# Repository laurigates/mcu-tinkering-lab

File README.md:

# MCU Tinkering Lab

A monorepo of microcontroller projects, mostly ESP32. The largest is a robot car
that drives on camera input and an LLM's plan. Others cover audio toys, game
controller bridges, an ESP-NOW mesh of companion boxes, and a self-balancing
robot on the RP2350.

## Flash from the browser

Released firmware can be flashed with the
[web flasher](https://laurigates.github.io/mcu-tinkering-lab/) in Chrome or
Edge, with no toolchain installed. Board-specific boot-mode notes are on the
page itself ([source](docs/flasher/index.html)).

The [robocar board story](https://laurigates.github.io/mcu-tinkering-lab/robocar/)
follows the robot car from a 2018 kit to a generated, factory-made carrier
board ([source](docs/site/robocar/index.html)). The
[balancebot story](https://laurigates.github.io/mcu-tinkering-lab/balancebot/)
follows the self-balancing robot from its first firmware to standing in place
([source](docs/site/balancebot/index.html)).

## Build from source

ESP-IDF builds run in a container, so Docker and
[just](https://github.com/casey/just) are the only requirements.

```bash
git clone https://github.com/laurigates/mcu-tinkering-lab.git
cd mcu-tinkering-lab
just setup-all                   # Docker images, dev tools, pre-commit hooks
just list-projects               # every project module
just robocar::build              # build one
```

Build, test and CI details are in [CONTRIBUTING.md](CONTRIBUTING.md).

## Projects

| Domain | Projects |
|---|---|
| `robotics/` | [AI robot car](packages/robotics/robocar/README.md): single-board firmware (XIAO ESP32-S3 Sense), its [integrated carrier](packages/robotics/robocar/integrated/README.md), [bring-up self-test](packages/robotics/robocar/bringup/README.md), a [Pymunk plant model](packages/robotics/robocar/simulation/README.md) and a [behaviour twin](packages/robotics/robocar/twin/README.md). [Self-balancing robot](packages/robotics/balancebot/README.md) (XIAO RP2350, Pico SDK) |
| `thinkpack/` | ESP-NOW mesh of companion boxes: brainbox (LLM coordinator), boombox, chatterbox, finderbox, glowbug, mesh-demo |
| `camera-vision/` | MJPEG webserver, camera + I2S audio, LLM Telegram bot, Gemini object detection |
| `audio/` | BLE gamepad synth, kids' audio toy, melody detector, RFID audiobook player (ESPHome) |
| `input-gaming/` | Xbox → Switch bridge, Switch USB proxy, LEGO Boost with an Xbox controller |
| `networking/` | IT troubleshooter, WiFi AP test, WireGuard + Home Assistant (ESPHome) |
| `sensors/` | 24 GHz mmWave presence sensor (ESPHome) |
| `usb-tools/` | ESP32-S3 raw USB relay for facedancer |
| `games/` | NFC scavenger hunt |
| `components/` | Shared ESP-IDF components: Improv WiFi provisioning, GitHub Releases OTA, ThinkPack libraries |

Most projects have a README in their directory.

## Documentation

- [docs/](docs/README.md): architecture decisions, requirements, board
  references, schematics
- [CONTRIBUTING.md](CONTRIBUTING.md): development setup, build commands,
  testing, CI, adding a project

## License

MIT ([LICENSE](LICENSE)), except the two vendored KiCad libraries under
`tools/kicad/lib/`, which keep their upstream licences:
[`kicad-stock/`](tools/kicad/lib/kicad-stock/) is a subset of the KiCad
libraries under CC-BY-SA 4.0 with KiCad's design exception
([LICENSE.md](tools/kicad/lib/kicad-stock/LICENSE.md)), and
[`seeed-xiao/`](tools/kicad/lib/seeed-xiao/) is Seeed Studio's, under their MIT
licence ([LICENSE](tools/kicad/lib/seeed-xiao/LICENSE)).

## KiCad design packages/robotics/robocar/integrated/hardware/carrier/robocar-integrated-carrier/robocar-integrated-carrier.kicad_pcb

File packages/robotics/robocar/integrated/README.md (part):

# Robocar: integrated carrier

The [robocar](../) carrier PCB with the chips on the board itself:
no breakout modules and no buck module. It exists to compare the two approaches.
The firmware, the pin header (`../main/pin_config.h`) and the three head
boards are robocar's, unchanged. There is no firmware here.

> **PROVISIONAL: do not order.** The board is placed by hand, routed by Freerouting
> and passes every carrier gate (ERC, DRC with schematic parity, netlist parity,
> the board check and its stamp). One adversarial layout review has been run and
> its findings fixed (see [Before ordering](#before-ordering)); the fixed board
> has not been reviewed again, and the bench items there stand.

## What changes

| Socketed carrier (`../hardware/carrier`) | Integrated carrier (here) |
|---|---|
| A3 Adafruit TCA9548A breakout | U5 TCA9548APWR (TSSOP-24), C5, upstream I2C pull-ups R14/R15, RESET pull-up R16 |
| A2 Adafruit PCA9685 breakout | U6 PCA9685PW (TSSOP-28), C4; series R17-R24 on the LED and servo channels (220 Ω, 47 Ω on green and blue) |
| A1 SparkFun TB6612FNG breakout | U7 TB6612FNG (SSOP-24), C15 (VCC), C16 (VM) |
| A4 Adafruit MAX98357A breakout | U8 MAX98357AETE+ (TQFN-16), C17, C18, ferrite bead FB1 on its supply |
| A5 CJMCU-2317 (MCP23017) module | U9 MCP23017-E/SS (SSOP-28), C6 |
| J4 lead to an LM2596 module | U10 TPS563208 (SOT-23-6, 3 A), L1 4.7 µH, C9-C14 and C20, feedback R12/R13, EN cutoff divider R25/R26, input bulk C19 |
| (no fuse) | Q1 reverse-polarity P-FET and F1 3 A PTC between the XT30 and VBAT, [below](#design-notes) |
| C1-C3 470 µF electrolytics (8 x 10.5 mm) | C1-C3 22 µF tantalums (3528), [below](#bulk-capacitors) |
| Servos and LEDs on the PCA9685 breakout's 3-pin columns | J20/J21 servo headers, J22/J23 RGB LED headers |
| Speaker on the MAX98357A breakout's screw terminal | J19 JST-XH 2 |

Everything else keeps its reference, value and role: the connectors, the test
headers, the LDO, the mux channel pull-ups, the buzzer, the mounting holes and
the three head boards (U1/J2, and the spares U3/J16 and U4/J17). Net names are the socketed carrier's, so the two netlists compare
by name.

## Footprint comparison

The laid-out boards, as cut apart (by hand saw, [below](#panel-hand-saw):
the line between the main board and the heads
takes about 1 mm from each, so the main board is 63.5 mm wide once separated):

| Main board | Socketed | Integrated |
|---|---|---|
| Size | about 70.5 x 100 mm | 64.5 x 76 mm |
| Area | about 7050 mm² | 4902 mm² (−30 %) |

| Whole PCB | Socketed | Integrated |
|---|---|---|
| Outline | 100 x 100 mm | 94 x 100 mm |

Both PCBs carry the same three head boards, the 29.5 mm square for the pan-tilt
cradle, in a column on the right: the integrated column is the socketed one moved
6 mm left. The integrated main board ends at y 76, so the strip below it
(64.5 x 24 mm) is waste; the outline stays 100 mm tall for the heads. J3's
courtyard ends 0.06 mm short of the y 76 line (`carrier-review`): saw that
line on the waste side. The integrated main board keeps
the socketed one's layout habits (connectors along the front and rear edges, M3
holes in the corners, 0.5 mm edge keepouts), so the difference is the chips, not a
tighter layout style. Its parts' courtyards fill half of it; the socketed board's
fill three quarters.

The parts alone:

```bash
just robocar-integrated::compare
```

prints each carrier's courtyard area, grouped into main board, head board and
mounting holes, then every main-board part only one carrier has
(`tools/kicad/area.py`). Each part counts its courtyard's bounding box: for a
breakout socket that is the module's outline, for a bare chip the package and its
pads. The sum is a lower bound on board area; it leaves out routing and the gaps a
placement leaves. As of this commit:

| Main board | Socketed | Integrated |
|---|---|---|
| Parts | 40 | 77 |
| Courtyard area | 5381 mm² | 2298 mm² (−57 %) |
| SMD / through-hole parts | 20 / 20 | 58 / 19 |
| Pads | 202 | 316 |

Where the area goes:

- The 31 parts the two main boards share take 1362 mm². Most of it is the
  connectors, the 2x10 GPIO mirror header and the M3 holes' surroundings, none of
  which shrink.
- The five breakout sockets and the buck lead take 3687 mm²; the PCA9685 breakout
  alone is 63 x 26 mm (1625 mm²). Their replacements, 46 parts, take 936 mm²:
  the six chips 356 mm², the buck's inductor 46 mm² and input bulk capacitor
  67 mm², 29 0805 passives and the ferrite bead 208 mm², the tantalums 52 mm²,
  D1 11 mm², and the new servo, LED and speaker connectors 197 mm².
- The three 470 µF electrolytics (332 mm²) became 22 µF tantalums (52 mm²).
- The socketed carrier's buck converter is off the board: the LM2596 module (about
  43 x 21 mm) sits on the chassis at the end of J4's lead. The integrated buck
  (U10, L1, eight capacitors, four resistors) adds about 220 mm² of courtyard
  to the board and removes the module.

Other differences the numbers do not show:

- **Assembly.** Every new part is SMD. TSSOP and SSOP at 0.65 mm pitch hand-solder
  with flux and care; the MAX98357A's TQFN with its exposed pad needs hot air or
  JLCPCB assembly. The socketed carrier needs no fine-pitch soldering.
- **Repair.** A dead breakout unplugs; a dead chip is a rework job.
- **Debug.** The breakouts' own pins are no longer there to probe. J11 and J12
  (supply and I2C test headers) are unchanged; there is no test point on the
  motor-driver inputs or the I2S lines.
- **Height.** The breakouts sat on sockets, about 10-15 mm above the board. The
  tallest integrated parts are the headers and the XT30; C19 is 7.7 mm.

## JLCPCB assembly

Every SMD part on the front carries an LCSC number (#808), so JLCPCB can
assemble the whole main board. `just robocar-integrated::carrier-fab`
writes `output/assembly/<name>-bom-jlc-<sha7>.csv` and
`<name>-cpl-jlc-<sha7>.csv`, named for the commit: 25 BOM lines, 60
placements, one per SMD part. The chips and the inductor take their number
from their registry entry (`docs/reference/parts/`), the passives from
`hardware.toml`.

| Ref | Part | LCSC | Library |
|---|---|---|---|
| U5 | TCA9548APWR | C130026 | Extended |
| U6 | PCA9685PW,118 | C2678753 | Extended |
| U7 | TB6612FNG (SSOP-24, 5.3 mm) | C88224 | Extended |
| U8 | MAX98357AETE+T | C910544 | Extended |
| U9 | MCP23017-E/SS | C506653 | Extended |
| U10 | TPS563208DDCR | C468250 | Extended |
| U2 | AMS1117-3.3 | C6186 | Basic |
| L1 | Bourns SRN6045TA-4R7M | C2044594 | Extended |
| F1 | BSMD1812-300-16V, 3 A hold, 16 V | C883162 | Extended |
| Q1 | DMP3013SFV-7 P-MOSFET, PowerDI3333-8 | C264098 | Extended |
| D1 | B5819W Schottky, SOD-123 | C8598 | Basic |
| FB1 | Murata BLM21PG221SN1D, 220 Ω, 2 A, 45 mΩ | C85840 | Extended |
| C19 | 100 µF 35 V electrolytic, 6.3 x 7.7 mm | C2836437 | Extended |
| C1-C3, C7, C8 | 22 µF 16 V tantalum, 3528 | C8020 | Extended |
| C13, C14, C20 | 22 µF 25 V X5R 0805 | C45783 | Basic |
| C9, C11, C16, C17, C21 | 10 µF 25 V X5R 0805 | C15850 | Basic |
| C4-C6, C10, C12, C15, C18 | 100 nF 50 V X7R 0805 | C49678 | Basic |
| R2-R11, R14, R15 | 2.2 kΩ 0805 | C17520 | Basic |
| R13, R16, R27 | 10 kΩ | C17414 | Basic |
| R12 | 56 kΩ | C17756 | Extended |
| R25 | 100 kΩ | C149504 | Basic |
| R26 | 36 kΩ | C4360 | Extended |
| R17, R20, R23, R24 | 220 Ω | C17557 | Basic |
| R18, R19, R21, R22 | 47 Ω | C17714 | Basic |
| R1 | 100 Ω | C17408 | Basic |

Stock and library type are JLCPCB's listing on 2026-10-19. The thinnest stock
is the inductor (179) and the MCP23017 (424); check both before ordering.
Q1 (C264098) is Extended, 3,409 in stock on 2026-10-22. 56 kΩ
(R12, see Buck converter) has no Basic part and costs one Extended fee, as TI's
54.9 kΩ did; so does 36 kΩ (R26, see Pack voltage), 93,700 in stock on
2026-10-21. JLCPCB lists no 56.2 kΩ.

### Placement rotation

JLCPCB places each part as LCSC's own footprint draws it, and LCSC draws most of
these chips with pin 1 bottom-left where KiCad has it top-left.
[`docs/reference/jlcpcb-rotations.toml`](../../../../docs/reference/jlcpcb-rotations.toml)
holds the offset per LCSC number, derived by `kicad.lcsc_rotation` from LCSC's
footprint pad by pad, and `kicad.jlc` adds it to KiCad's rotation in
`cpl-jlc.csv`: 270° for U5, U7, U8, U9, U10 and Q1, 180° for U2, 0° for U6
(the PCA9685PW's LCSC footprint has pin 1 top-left) and for every two-pad part.
Without it the CPL would have put five chips at 90° and the LDO at 180°.
`carrier-fab` fails on a placed LCSC number with no checked offset. JLCPCB's
preview is still the last check: compare each chip's pin-1 dot with the
silkscreen before paying.

### Fiducials

Three fiducials, FID1-FID3 (1 mm copper, 2 mm mask opening), sit on the main
board in an asymmetric triangle: top-left (3.5, 9.5), top-right (60.5, 10.0)
and bottom-left (3.5, 66.5), each 2 mm clear of every courtyard. JLCPCB does not
require them for a board this size; they let the machine correct for board
stretch, which the 0.5 mm-pitch TQFN is least tolerant of.

### What is still hand-soldered

The through-hole parts: the XT30 (J3), the motor, speaker, rangefinder and OLED
connectors (J5-J9, J19), the ribbon header (J1), the servo and LED headers
(J20-J23), the test and ground headers (J11-J15), the GPIO mirror header (J18),
the buzzer (BZ1), and on the heads the XIAO sockets (U1, U3, U4) and their
ribbon headers (J2, J16, J17). All are 2.5 mm pitch or wider.

After soldering the XT30 (J3), inspect it for solder bridges: the unfused
pack input (PACK_IN, the 1.2 mm track from J3's + pin to Q1) runs between
J3's GND pin and F1's pad 1 at close to the board's 0.2 mm minimum
clearance, and a bridge there shorts the pack ahead of F1. Moving Q1 and F1
to open the gap does not fit: F1 would land on the 5V trunk.

### Cost

The order is five PCBs, the minimum, of which 2 or 5 can be assembled. The
outline is 94 x 100 mm on two layers, but that does not settle the price:
JLCPCB counts the pieces of one file as separate designs "as long as it can be
separated, no matter by v-cut, millings, or drill holes", and says it will
"usually charge more for this"
([Different Design in Your PCB Files](https://jlcpcb.com/help/article/different-design-in-your-pcb-files)).
The same page treats designs inside one outline with no v-cut lines, tabs or
milling slots, separated by the customer, as one design: that is this board,
cut apart by hand ([below](#panel-hand-saw)). A mouse-bite panel of the same
four pieces would count as four. No price has been seen, and coupons and
other offers change it from order to order. The part prices are fixed:

- **Parts:** about $11.50 per board at JLCPCB's listed unit prices
  (2026-10-19), plus Q1 at $1.23 (2026-10-22). The chips are most of it: PCA9685 $3.33, MCP23017 $1.77,
  MAX98357A $1.32, TB6612FNG $1.15, TCA9548A $0.81. Attrition parts come on
  top.
- **Extended parts:** 14 BOM lines, each with a per-order loading fee unless an
  offer waives it: the six chips, Q1, L1, F1, FB1, C19, the tantalums (C8020),
  R12 and R26. The other 11 lines are Basic, D1 included (JLCPCB's parts
  search, 2026-10-22).

## Panel: hand-saw

The main board and the three heads share one 94 x 100 mm PCB with a single
outline, cut apart by hand after delivery: `board.toml [panel] mode = "saw"`.
JLCPCB counts one outline with no slots, tabs or v-cuts as one design
([Cost](#cost)). The six cut lines are silkscreen (`[silk] cut_lines`), each
inside a copper-free keepout band.

**Saw on the waste side of each line, then file to the line.** On the y 70.5
line (head 2 above, head 3 below) the nearest copper is HEAD3_I2C_SDA, 0.79 mm
from the line; on every other line it is 1.00 mm or more (`carrier-review`).
A saw kerf of about 1 mm centred on the y 70.5 line would leave about 0.3 mm of
board over that track. The y 76 line under the main board passes 0.06 mm from
J3's courtyard (the XT30 body), so saw that one on the waste side too. The
x 64.5 line between the main board and the heads has no waste strip: the two
share it, so saw on the line and the kerf comes out of both (about 1 mm each,
[Footprint comparison](#footprint-comparison)). Check a cut head against the
cradle's 30 x 30 mm square before relying on the fit. Cutting FR-4 makes
glass-fibre dust; cut wet or with a mask.

Head 3's band keepout ends at y 71.0, not the 71.5 a saw kerf would want: at
71.5, with the keepouts under head 3's screw heads (H9, H10), HEAD3_PIEZO (J17:8
to U4:2) stayed unrouted on 5 of 5 routes.

The board's outputs, checked after `carrier-fab`: 10 non-plated holes (the
mounting holes), a 4-segment outline, no slots.

The mouse-bite panel (#809, `tools/kicad/panel.py`) is still in `board.toml`
as `[[panel.lines]]`: `mode = "mousebites"` turns the cut lines into 2 mm
Edge.Cuts slots and 14 tabs of 0.6 mm non-plated holes. It was this board's
mode until the seventh review; JLCPCB would count that panel as four designs.

**Quotes:** not taken yet. Record the bare and assembled prices here.

## Design notes

The circuit choices that are not a copy of a breakout:

- **Buck converter.** TPS563208: 4.5-17 V in, 3 A out, matching the LM2596
  module's rating. It is the forced-continuous sibling of the TPS563201, with
  the same pins and the same TI SLVSD90B Table 7-2 values, chosen because it
  sinks current as well as sourcing it: a motor that brakes or reverses pushes
  energy back into 5 V through the TB6612FNG, and a pulse-skipping converter
  would leave that to charge the rail (whose absolute maximum, at the
  MAX98357A, is 6 V). For 5 V: R12 56 kΩ over R13 10 kΩ (TI's R1 and R2,
  whose Table 7-2 gives 54.9 kΩ for 4.98 V). VFB is 0.768 V (749-787 mV), so
  5V is 5.07 V (4.94-5.19 V). At typical VFB, less the trunk's roughly 50 mV
  at 2 A, VM stays in the TB6612FNG's VM >= 5 V row (1.0 A per channel); at
  VFB's minimum, 4.94 V, it falls in the 0.4 A row. Either way it stays under
  the MAX98357A's 5.5 V. The 5 V and 6.5 V rows share L1 and Cout. L1 4.7 µH ±20 % (Bourns SRN6045TA-4R7M: Isat 6.8 A, Irms 4.5 A,
  above the 5.5 A peak at the 5.1 A maximum current limit), since the 3.3 µH
  part is ±30 % and can fall below the table's 3.3 µH minimum; 3 x 22 µF 0805
  out (C13, C14, C20), since an 0805 keeps roughly half its capacitance at
  5 V and two can fall under the table's 20 µF minimum.
- **Pack voltage.** The converter's maximum recommended duty cycle is 75 %
  (SLVSD90B §7.3, Power Supply Recommendations), so 5 V needs VIN ≥ 6.7 V, 3.3 V per cell; below that 5 V sags with
  the pack. EN goes through a 100 kΩ / 36 kΩ divider (R25/R26), with EN's own
  resistance to GND (600-2400 kΩ, SLVSD90B 5.5) in parallel with R26: EN rises at
  1.38-1.47 V typical (VENH 1.6 V maximum) and falls at 1.05-1.2 V, so the buck
  turns on at about 5.5 V typical, is guaranteed on by 6.3 V, and turns off at
  about 4.0-4.6 V, below TI's 4.5 V minimum recommended input (SLVSD90B 5.3),
  so between about 4.0 and 4.5 V the buck runs outside its specified range
  until it stops. With 30 kΩ the guarantee was 7.2 V, so a part-charged pack
  could fail to start it. The cutoff is coarse, with no specified falling
  threshold: the pack carries an external 2S protection board (BMS) for its
  cells' undervoltage, overcurrent and short protection, and is charged with
  a 2S charger. F1, a 3 A hold PTC between Q1 and VBAT, limits a short on
  VBAT.
- **Reverse polarity.** Q1, a P-MOSFET high-side switch between the XT30 and
  F1 (drain to the XT30's +, source to F1, gate to GND through R27, 10 kΩ),
  as on the balancebot carrier: plugged in the right way the body diode
  conducts first and the gate sits the pack's voltage below the source, so
  the channel turns on; reversed, the body diode is reverse-biased and nothing
  on the board sees the pack. It is sized for this board's current, not the
  balancebot's SOT-223 ZXMP4A16G (100 mΩ at VGS −4.5 V, 0.9 W at 3 A):
  DMP3013SFV (Diodes DS40141 Rev. 5-2) has VDSS −30 V, VGSS ±25 V and
  RDS(on) at most 9.5 mΩ at −10 V and 17 mΩ at −4.5 V, so 0.15 W at 3 A and
  0.51 W at 5.5 A, the buck's current-limit peak; at the minimum-pad 134 °C/W
  that is about 20 °C and 69 °C over ambient. |VGS| follows the pack, 8.4 V
  charged and 6.7 V where the buck stops regulating; below 4.5 V, as the EN
  cutoff nears, RDS(on) is not specified. No gate zener: a 2S pack's undamped
  hot-plug ring reaches at most 16.8 V, under the 25 V VGSS (the balancebot's
  3S ring reaches 25.2 V against a 20 V part). Not measured on a board.
- **5 V current budget.** Nothing in the repo names the drive motors; the
  simulation assumes 3 Ω windings and a 2 A stall (`../simulation/config/
  robot_config.yaml`), which is about 1.7 A each at 5 V. Two stalled motors
  (3.4 A) alone pass the buck's 3.3 A minimum current limit, before the
  servos (about 0.7 A each at stall), the head (about 0.5 A) and the amplifier
  (about 1 A peaks). Past the limit the converter hiccups (10 ms restarts)
  and resets the XIAO. Measure the real motors' stall current; if it is near
  this, ramp and cap the PWM duty in firmware, or give the motors their own
  supply.
- **Bulk capacitors.** D-CAP2 regulates on the output ripple, and its stability
  rests on the L x Cout double pole; TI bounds Cout at 68 µF of low-ESR
  capacitance. The socketed carrier's three 470 µF electrolytics made up for an
  LM2596 module at the end of a lead; next to this buck, a low-ESR polymer of the
  same value would sit inside the loop and could make it unstable, and so could
  the electrolytics. C1-C3 are 22 µF MnO2 tantalums (3528, the LDO's part). Their
  ESR (about 1.5 Ω) is not enough to take them out of the loop: at the LC
  double pole, near 18 kHz, the tantalums on 5V look like about 0.4 Ω in
  parallel, about the ceramics' reactance there, so they damp the pole rather
  than move it. That is probably benign but outside TI's table: bench-test a
  0.2-2 A load step before trusting it. On AMP_5V the tantalum damps FB1
  against C17, a ferrite and a ceramic alone being a resonant LC. The input side has no such
  limit, so C19 (100 µF 35 V, 6.3 x 7.7 mm) is an aluminium electrolytic on VBAT:
  its ESR damps the ringing of the battery lead's inductance against the ceramic
  input capacitors when the XT30 is plugged in, which a polymer would not, and a
  tantalum takes that surge badly. The motors' stall current now draws on the
  buck's 3 A and C2 rather than a 470 µF reservoir; check for brown-outs on the
  bench.
- **Strapping.** Mux, PWM driver and expander address pins go straight to GND
  (0x70, 0x40, 0x20, as `pin_config.h` expects). The PCA9685's OE and EXTCLK go to
  GND, the MCP23017's RESET to 3V3. The MAX98357A keeps the socketed carrier's
  straps: SD_MODE to VDD (left channel), GAIN_SLOT to GND (12 dB).
- **PCA9685 outputs.** The Adafruit breakout has a 220 Ω resistor on every output;
  they are kept only on the channels that leave the board (LEDs, servos). The six
  motor-driver channels go straight to the TB6612FNG.
- **Amplifier supply.** The MAX98357A takes 5 V through a ferrite bead (FB1) as
  its own net, AMP_5V, with SD_MODE, its decoupling and its 22 µF bulk capacitor.
  It keeps the class-D switching off the motor and logic rail, and it is what lets
  5 V have tracks wider than the amplifier's pins allow (below). Choose a bead
  rated for at least 2 A.
- **RGB LEDs.** Common anode on 3V3, the PCA9685's own supply, so an output driven
  high leaves no forward voltage across the LED. The LEDs' resistors are on this
  board (R17-R22): 220 Ω on red (about 6 mA at 2 V), 47 Ω on green and blue,
  whose 2.9-3.2 V forward voltage leaves next to nothing across 220 Ω from 3V3
  (about 4-6 mA through 47 Ω).
- **I2C pull-ups** are 2.2 kΩ, upstream (R14/R15) and on every mux channel
  (R2-R11), as on the socketed carrier since #810: at 400 kHz, Fast-mode's
  300 ns rise time allows 10 kΩ only below about 35 pF of bus. RESET's R16
  stays 10 kΩ.
- **LCSC numbers** are set on every SMD part: see
  [JLCPCB assembly](#jlcpcb-assembly).

## Layout

`hardware/carrier/board.toml` holds the placement, the fixed tracks, the net
classes, the pour and the silkscreen. The buck converter follows TI's layout
order: SW straight into L1, the input capacitors beside VIN, the output
capacitors on L1's output pad, the bootstrap capacitor along VBST's side and
straight down to the switch node at L1, the feedback divider beside FB with
its own sense track from the output capacitors.

Freerouting gives each net one track width, so a net class is the widest track every
pin on its nets accepts:

| Class | Nets | Track | Limited by |
|---|---|---|---|
| input_power | PACK_IN, VBAT, BUCK_SW | 0.8 mm | TPS563208 pads, 0.6 mm at 0.95 mm pitch |
| five_volt | +5V, XIAO_5V | 0.8 mm, 1.0/0.5 mm vias | none: the 0.8 mm track lands on the TB6612FNG's 0.4 mm pins, 0.202 mm from their neighbours |
| motor_power | MOT_* | 0.45 mm | TB6612FNG pads |
| head_power | HEAD*_XIAO_5V, HEAD*_GND | 0.5 mm | |
| logic_power | +3V3 | 0.35 mm | |
| signal | everything else | 0.25 mm | MAX98357A pads, 0.25 mm at 0.5 mm pitch |

Tracks laid down before routing (`[[tracks]]`, locked on the board):

- **Pack input**, 1.2 mm from the XT30 to Q1's drain, through the 1.65 mm
  slot between F1's pad 1 and the XT30's GND pin (a 3.5 mm rounded square),
  then Q1's source pads tied along their row and 1.5 mm into F1: it carries
  the whole robot's current. `carrier-measure path`/`resistance`: J3:2 to
  Q1:5 3.48 mm, ~1.53 mΩ; Q1:1 to F1:1 2.30 mm, ~0.53 mΩ.
- **Q1's gate**, 0.3 mm to R27.
- **Servo ground**, 0.8 mm on F.Cu from U6's GND pin 1 to the servo header
  J21:3, between R17 and R18 (R17 sits 0.6 mm north of the column pitch to
  make the gap). Routed, the servos' ground reached the plane through one
  0.25 mm track (seventh review, SF2).
- **Buck output node**, C13 to C14 to C20 to L1's output pad (1 mm, then 2 mm):
  the output capacitors on the inductor, which every 5 V load hangs off.
- **5V trunk**, 1.5 mm on F.Cu from L1's output pad west and north to C2, beside
  the TB6612FNG's VM pins and C16.
- **East 5V branch**, 1 mm from C20 to C7, then on to the LDO (U2) and up to
  the amplifier's ferrite (FB1).
- **5V sense**, 0.25 mm from C20 to the feedback divider's top (R12), east of
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
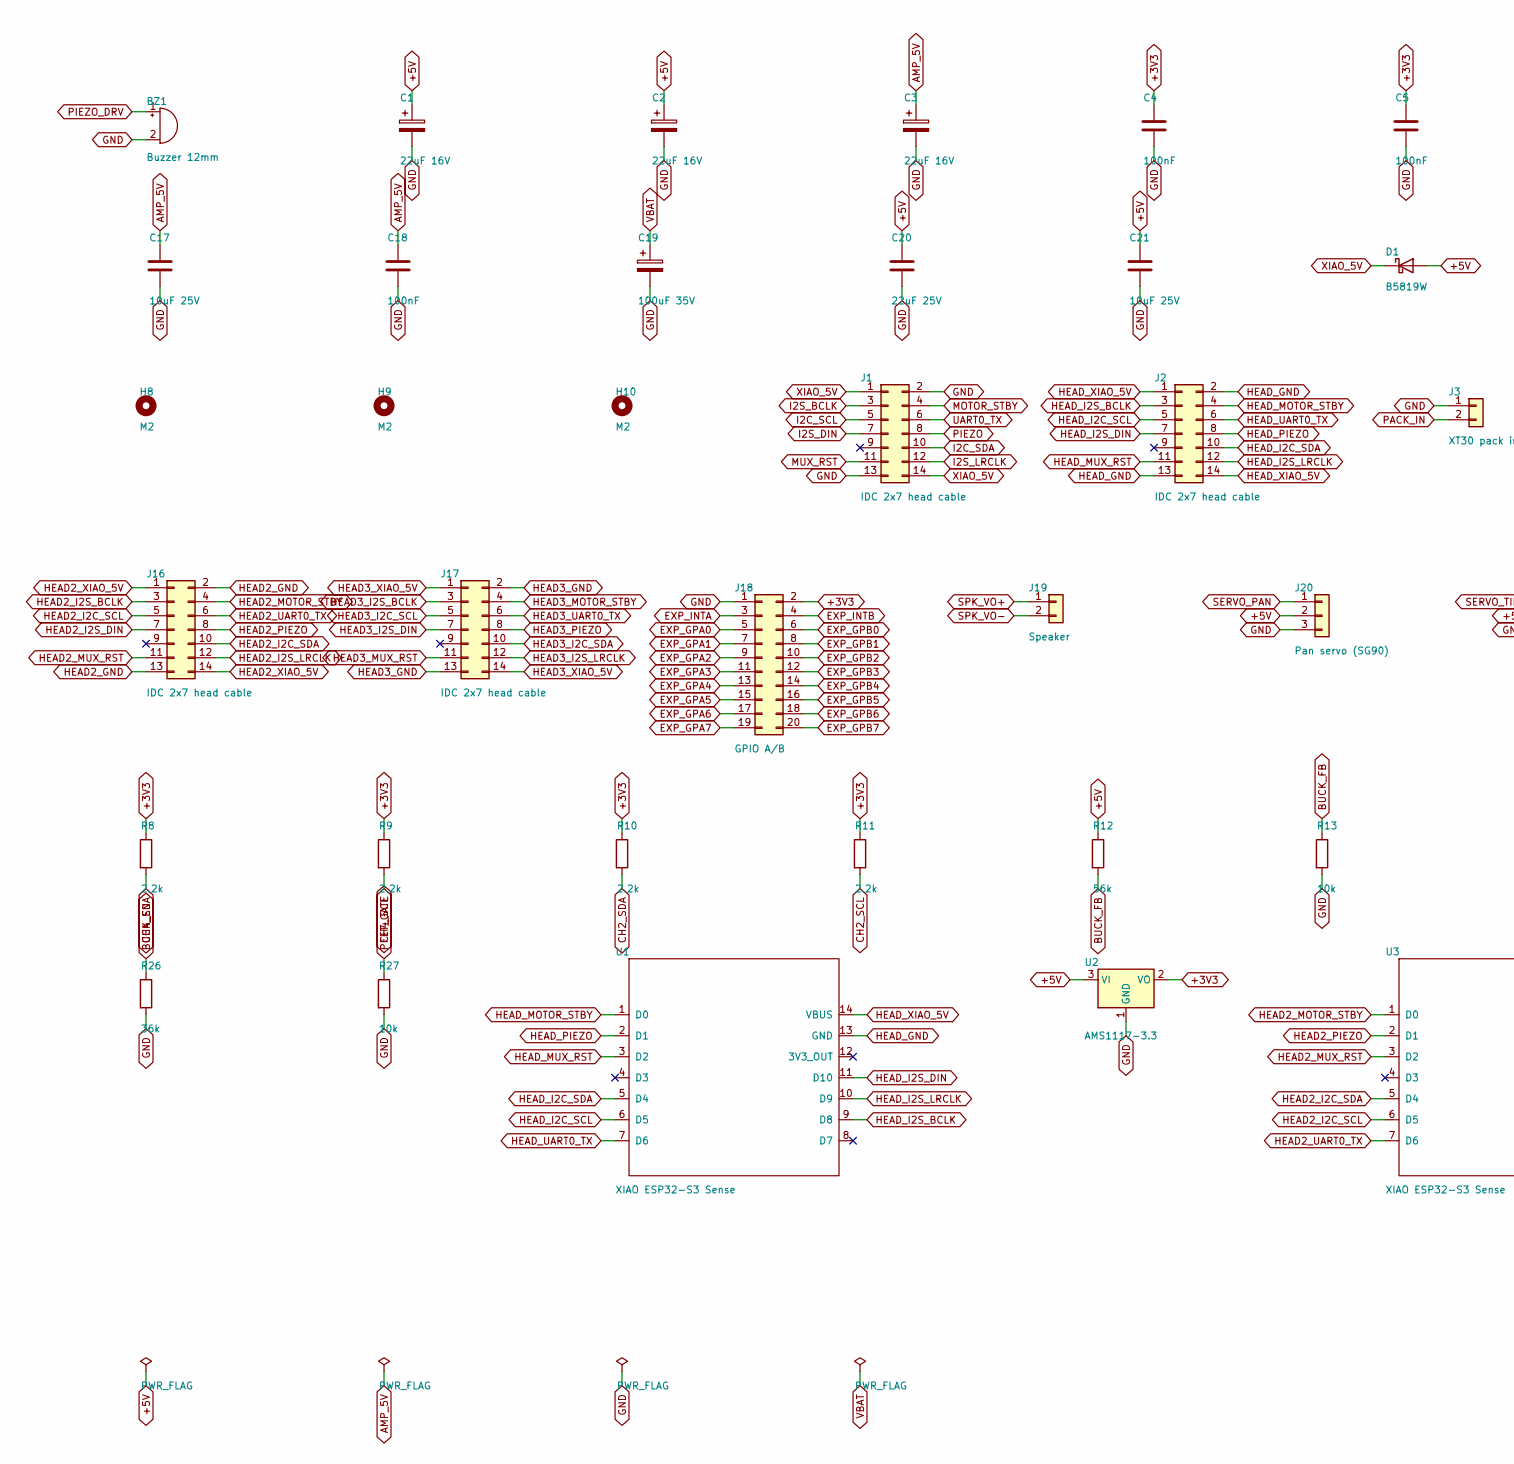
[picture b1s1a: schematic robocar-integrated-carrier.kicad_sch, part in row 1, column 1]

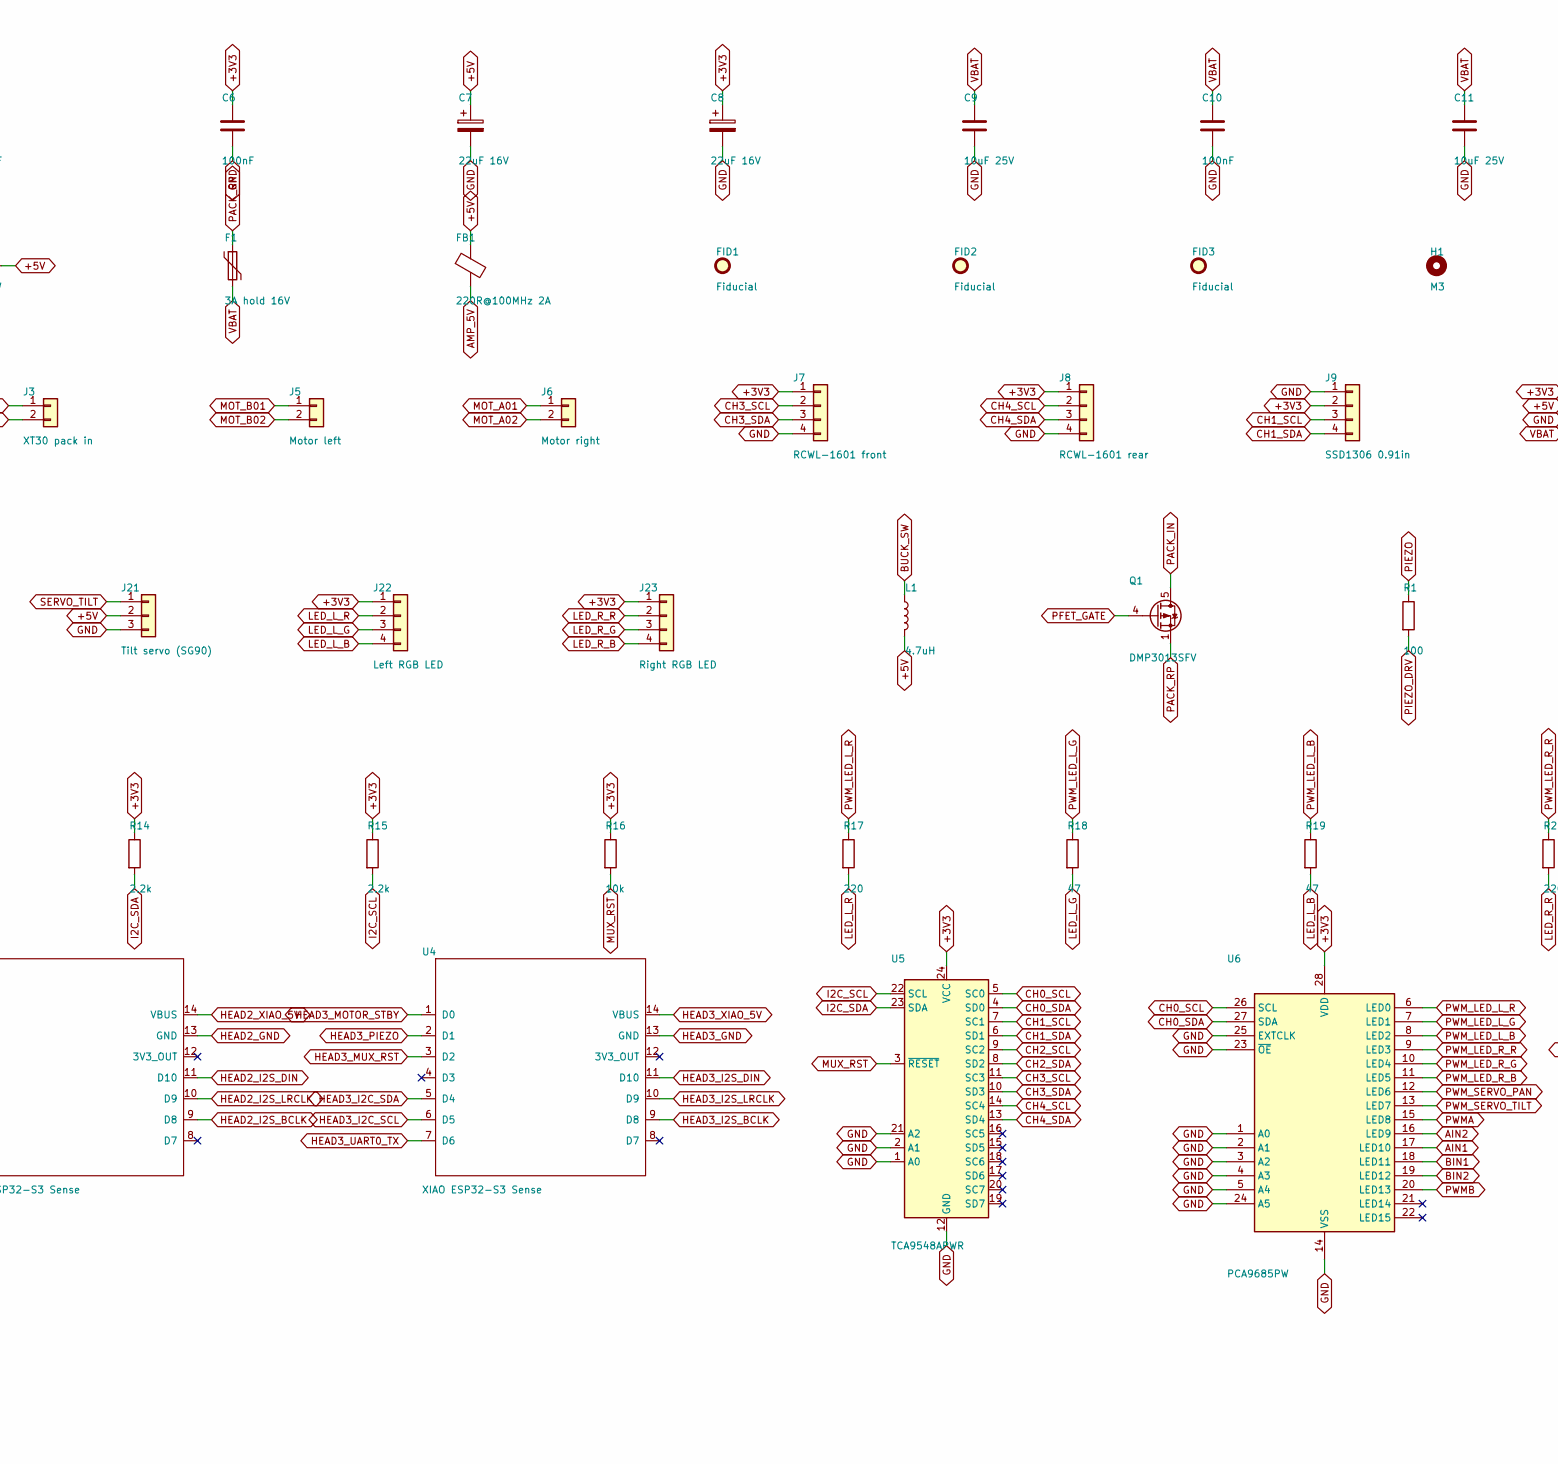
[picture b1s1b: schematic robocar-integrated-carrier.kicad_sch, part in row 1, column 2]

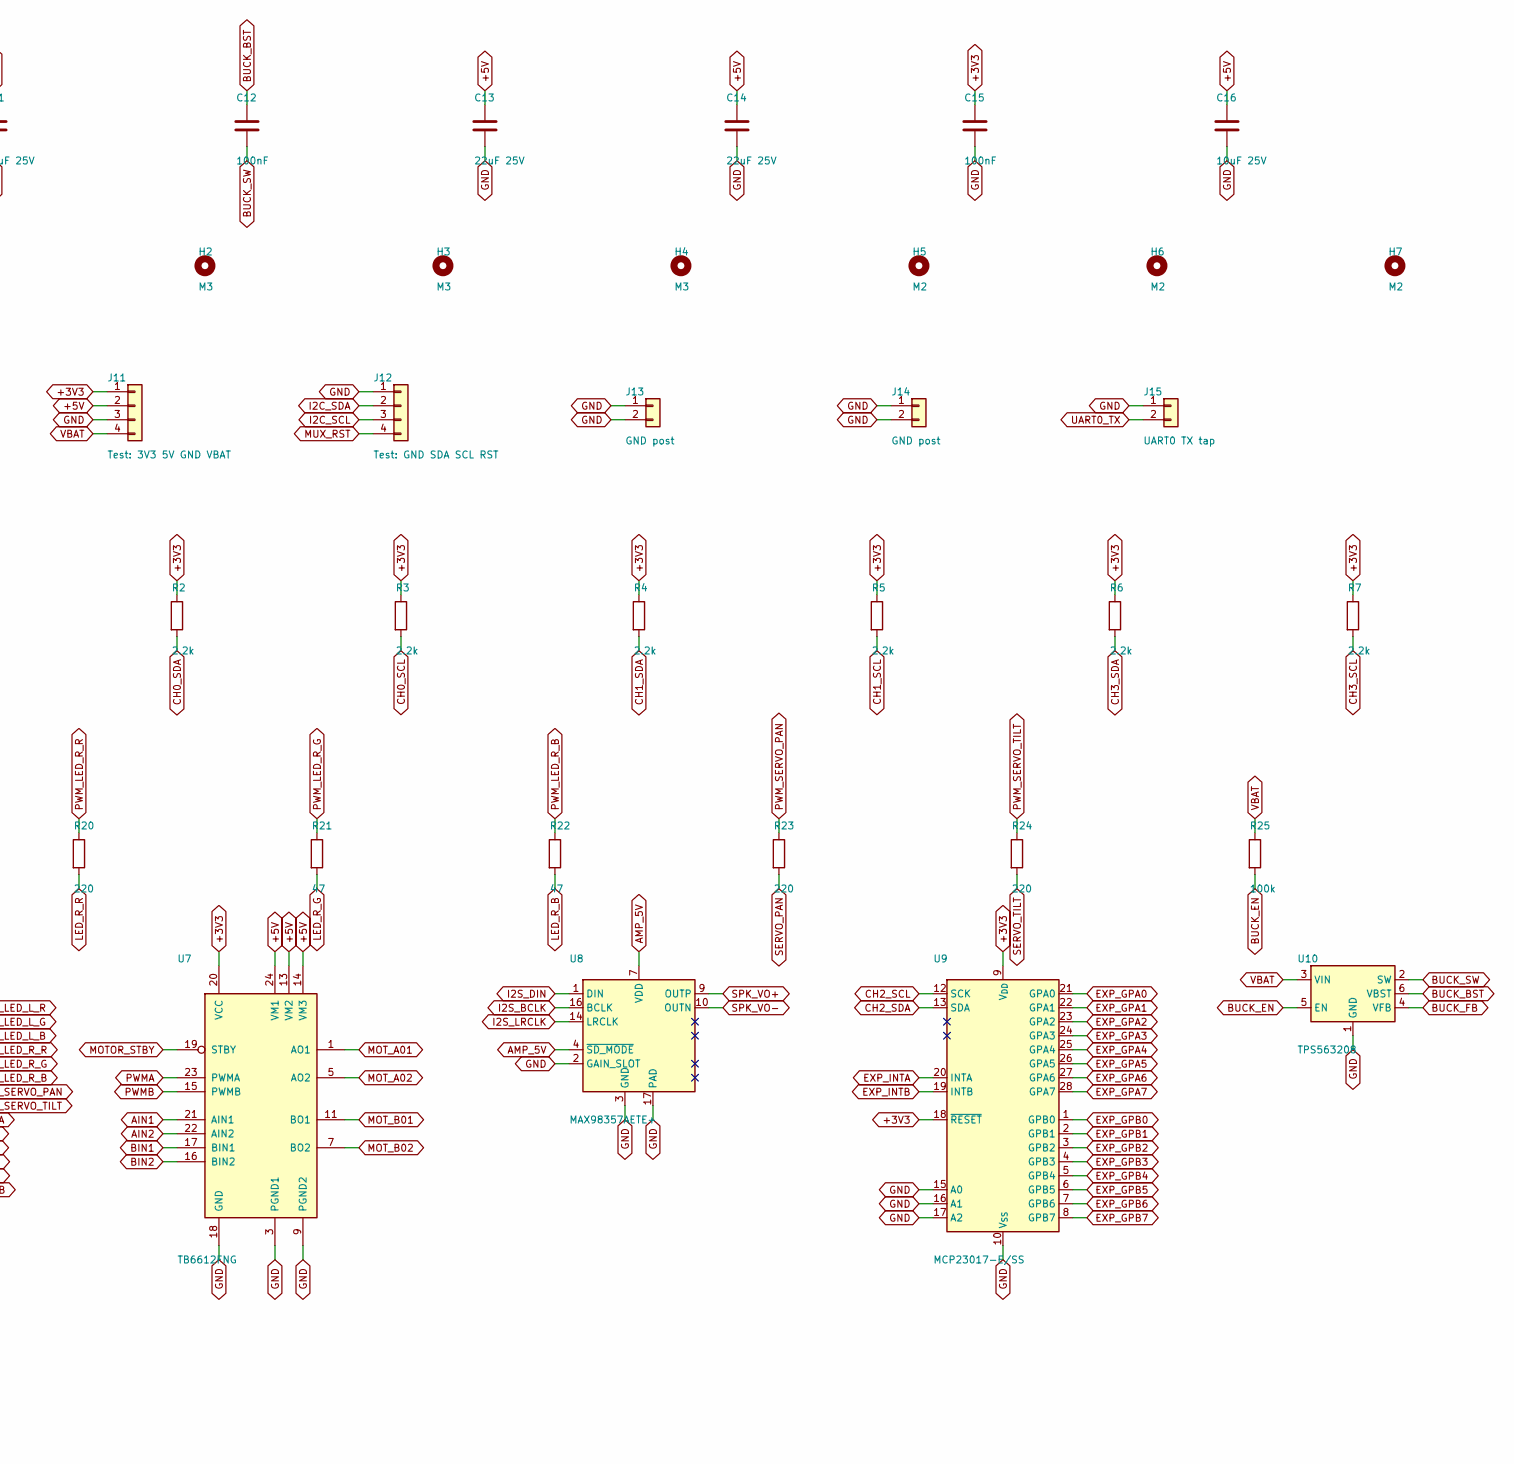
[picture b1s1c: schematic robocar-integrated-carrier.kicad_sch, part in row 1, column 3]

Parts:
BZ1: Buzzer 12mm; Buzzer_12x9.5RM7.6
C1, C2, C3, C7, C8: 22uF 16V; CP_EIA-3528-21_Kemet-B_HandSolder; LCSC C8020
C4, C5, C6, C10, C12, C15, C18: 100nF; C_0805_2012Metric_Pad1.18x1.45mm_HandSolder; LCSC C49678
C9, C11, C16, C17, C21: 10uF 25V; C_0805_2012Metric_Pad1.18x1.45mm_HandSolder; LCSC C15850
C13, C14, C20: 22uF 25V; C_0805_2012Metric_Pad1.18x1.45mm_HandSolder; LCSC C45783
C19: 100uF 35V; CP_Elec_6.3x7.7; LCSC C2836437
D1: B5819W; D_SOD-123; LCSC C8598
F1: 3A hold 16V; Fuse_1812_4532Metric_Pad1.30x3.40mm_HandSolder; LCSC C883162
FB1: 220R@100MHz 2A; L_0805_2012Metric_Pad1.05x1.20mm_HandSolder; LCSC C85840
FID1, FID2, FID3: Fiducial; Fiducial_1mm_Mask2mm
H1, H2, H3, H4: M3; MountingHole_3.2mm_M3
H5, H6, H7, H8, H9, H10: M2; MountingHole_2.2mm_M2_ISO7380
J1, J2, J16, J17: IDC 2x7 head cable; PinHeader_2x07_P2.00mm_Vertical
J3: XT30 pack in; AMASS_XT30PW-M_1x02_P2.50mm_Horizontal
J5: Motor left; JST_XH_B2B-XH-A_1x02_P2.50mm_Vertical
J6: Motor right; JST_XH_B2B-XH-A_1x02_P2.50mm_Vertical
J7: RCWL-1601 front; JST_XH_B4B-XH-A_1x04_P2.50mm_Vertical
J8: RCWL-1601 rear; JST_XH_B4B-XH-A_1x04_P2.50mm_Vertical
J9: SSD1306 0.91in; JST_XH_B4B-XH-A_1x04_P2.50mm_Vertical
J11: Test: 3V3 5V GND VBAT; PinHeader_1x04_P2.54mm_Vertical
J12: Test: GND SDA SCL RST; PinHeader_1x04_P2.54mm_Vertical
J13, J14: GND post; PinHeader_1x02_P2.54mm_Vertical
J15: UART0 TX tap; PinHeader_1x02_P2.54mm_Vertical
J18: GPIO A/B; PinHeader_2x10_P2.54mm_Vertical
J19: Speaker; JST_XH_B2B-XH-A_1x02_P2.50mm_Vertical
J20: Pan servo (SG90); PinHeader_1x03_P2.54mm_Vertical
J21: Tilt servo (SG90); PinHeader_1x03_P2.54mm_Vertical
J22: Left RGB LED; PinHeader_1x04_P2.54mm_Vertical
J23: Right RGB LED; PinHeader_1x04_P2.54mm_Vertical
L1: 4.7uH; L_Bourns_SRN6045TA; LCSC C2044594
Q1: DMP3013SFV; Diodes_PowerDI3333-8; LCSC C264098
R1: 100; R_0805_2012Metric_Pad1.20x1.40mm_HandSolder; LCSC C17408
R2, R3, R4, R5, R6, R7, R8, R9, R10, R11, R14, R15: 2.2k; R_0805_2012Metric_Pad1.20x1.40mm_HandSolder; LCSC C17520
R12: 56k; R_0805_2012Metric_Pad1.20x1.40mm_HandSolder; LCSC C17756
R13, R16, R27: 10k; R_0805_2012Metric_Pad1.20x1.40mm_HandSolder; LCSC C17414
R17, R20, R23, R24: 220; R_0805_2012Metric_Pad1.20x1.40mm_HandSolder; LCSC C17557
R18, R19, R21, R22: 47; R_0805_2012Metric_Pad1.20x1.40mm_HandSolder; LCSC C17714
R25: 100k; R_0805_2012Metric_Pad1.20x1.40mm_HandSolder; LCSC C149504
R26: 36k; R_0805_2012Metric_Pad1.20x1.40mm_HandSolder; LCSC C4360
U1, U3, U4: XIAO ESP32-S3 Sense; XIAO-ESP32-S3-Socket
U2: AMS1117-3.3; SOT-223-3_TabPin2; LCSC C6186
U5: TCA9548APWR; TSSOP-24_4.4x7.8mm_P0.65mm; LCSC C130026
U6: PCA9685PW; TSSOP-28_4.4x9.7mm_P0.65mm; LCSC C2678753
U7: TB6612FNG; SSOP-24_5.3x8.2mm_P0.65mm; LCSC C88224
U8: MAX98357AETE+; TQFN-16-1EP_3x3mm_P0.5mm_EP1.23x1.23mm; LCSC C910544
U9: MCP23017-E/SS; SSOP-28_5.3x10.2mm_P0.65mm; LCSC C506653
U10: TPS563208; SOT-23-6; LCSC C468250

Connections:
+3V3: C4.1, C5.1, C6.1, C8.1, C15.1, J7.1, J8.1, J9.2, J11.1, J18.2, J22.1, J23.1, R2.1, R3.1, R4.1, R5.1, R6.1, R7.1, R8.1, R9.1, R10.1, R11.1, R14.1, R15.1, R16.1, U2.2 (VO), U5.24 (VCC), U6.28 (VDD), U7.20 (VCC), U9.9 (V_{DD}), U9.18 (~RESET)
+5V: C1.1, C2.1, C7.1, C13.1, C14.1, C16.1, C20.1, C21.1, D1.2 (A), FB1.1, J11.2, J20.2, J21.2, L1.2, R12.1, U2.3 (VI), U7.13 (VM2), U7.14 (VM3), U7.24 (VM1)
AIN1: U6.17 (LED10), U7.21 (AIN1)
AIN2: U6.16 (LED9), U7.22 (AIN2)
AMP_5V: C3.1, C17.1, C18.1, FB1.2, U8.4 (~SD_MODE), U8.7 (VDD), U8.8 (VDD)
BIN1: U6.18 (LED11), U7.17 (BIN1)
BIN2: U6.19 (LED12), U7.16 (BIN2)
BUCK_BST: C12.1, U10.6 (VBST)
BUCK_EN: R25.2, R26.1, U10.5 (EN)
BUCK_FB: R12.2, R13.1, U10.4 (VFB)
BUCK_SW: C12.2, L1.1, U10.2 (SW)
CH0_SCL: R3.2, U5.5 (SC0), U6.26 (SCL)
CH0_SDA: R2.2, U5.4 (SD0), U6.27 (SDA)
CH1_SCL: J9.3, R5.2, U5.7 (SC1)
CH1_SDA: J9.4, R4.2, U5.6 (SD1)
CH2_SCL: R11.2, U5.9 (SC2), U9.12 (SCK)
CH2_SDA: R10.2, U5.8 (SD2), U9.13 (SDA)
CH3_SCL: J7.2, R7.2, U5.11 (SC3)
CH3_SDA: J7.3, R6.2, U5.10 (SD3)
CH4_SCL: J8.2, R9.2, U5.14 (SC4)
CH4_SDA: J8.3, R8.2, U5.13 (SD4)
EXP_GPA0: J18.5, U9.21 (GPA0)
EXP_GPA1: J18.7, U9.22 (GPA1)
EXP_GPA2: J18.9, U9.23 (GPA2)
EXP_GPA3: J18.11, U9.24 (GPA3)
EXP_GPA4: J18.13, U9.25 (GPA4)
EXP_GPA5: J18.15, U9.26 (GPA5)
EXP_GPA6: J18.17, U9.27 (GPA6)
EXP_GPA7: J18.19, U9.28 (GPA7)
EXP_GPB0: J18.6, U9.1 (GPB0)
EXP_GPB1: J18.8, U9.2 (GPB1)
EXP_GPB2: J18.10, U9.3 (GPB2)
EXP_GPB3: J18.12, U9.4 (GPB3)
EXP_GPB4: J18.14, U9.5 (GPB4)
EXP_GPB5: J18.16, U9.6 (GPB5)
EXP_GPB6: J18.18, U9.7 (GPB6)
EXP_GPB7: J18.20, U9.8 (GPB7)
EXP_INTA: J18.3, U9.20 (INTA)
EXP_INTB: J18.4, U9.19 (INTB)
GND: BZ1.2 (-), C1.2, C2.2, C3.2, C4.2, C5.2, C6.2, C7.2, C8.2, C9.2, C10.2, C11.2, C13.2, C14.2, C15.2, C16.2, C17.2, C18.2, C19.2, C20.2, C21.2, J1.2, J1.13, J3.1, J7.4, J8.4, J9.1, J11.3, J12.1, J13.1, J13.2, J14.1, J14.2, J15.1, J18.1, J20.3, J21.3, R13.2, R26.2, R27.2, U2.1 (GND), U5.1 (A0), U5.2 (A1), U5.12 (GND), U5.21 (A2), U6.1 (A0), U6.2 (A1), U6.3 (A2), U6.4 (A3), U6.5 (A4), U6.14 (VSS), U6.23 (~OE), U6.24 (A5), U6.25 (EXTCLK), U7.3 (PGND1), U7.4 (PGND1), U7.9 (PGND2), U7.10 (PGND2), U7.18 (GND), U8.2 (GAIN_SLOT), U8.3 (GND), U8.11 (GND), U8.15 (GND), U8.17 (PAD), U9.10 (V_{SS}), U9.15 (A0), U9.16 (A1), U9.17 (A2), U10.1 (GND)
HEAD2_GND: J16.2, J16.13, U3.13 (GND)
HEAD2_I2C_SCL: J16.5, U3.6 (D5)
HEAD2_I2C_SDA: J16.10, U3.5 (D4)
HEAD2_I2S_BCLK: J16.3, U3.9 (D8)
HEAD2_I2S_DIN: J16.7, U3.11 (D10)
HEAD2_I2S_LRCLK: J16.12, U3.10 (D9)
HEAD2_MOTOR_STBY: J16.4, U3.1 (D0)
HEAD2_MUX_RST: J16.11, U3.3 (D2)
HEAD2_PIEZO: J16.8, U3.2 (D1)
HEAD2_UART0_TX: J16.6, U3.7 (D6)
HEAD2_XIAO_5V: J16.1, J16.14, U3.14 (VBUS)
HEAD3_GND: J17.2, J17.13, U4.13 (GND)
HEAD3_I2C_SCL: J17.5, U4.6 (D5)
HEAD3_I2C_SDA: J17.10, U4.5 (D4)
HEAD3_I2S_BCLK: J17.3, U4.9 (D8)
HEAD3_I2S_DIN: J17.7, U4.11 (D10)
HEAD3_I2S_LRCLK: J17.12, U4.10 (D9)
HEAD3_MOTOR_STBY: J17.4, U4.1 (D0)
HEAD3_MUX_RST: J17.11, U4.3 (D2)
HEAD3_PIEZO: J17.8, U4.2 (D1)
HEAD3_UART0_TX: J17.6, U4.7 (D6)
HEAD3_XIAO_5V: J17.1, J17.14, U4.14 (VBUS)
HEAD_GND: J2.2, J2.13, U1.13 (GND)
HEAD_I2C_SCL: J2.5, U1.6 (D5)
HEAD_I2C_SDA: J2.10, U1.5 (D4)
HEAD_I2S_BCLK: J2.3, U1.9 (D8)
HEAD_I2S_DIN: J2.7, U1.11 (D10)
HEAD_I2S_LRCLK: J2.12, U1.10 (D9)
HEAD_MOTOR_STBY: J2.4, U1.1 (D0)
HEAD_MUX_RST: J2.11, U1.3 (D2)
HEAD_PIEZO: J2.8, U1.2 (D1)
HEAD_UART0_TX: J2.6, U1.7 (D6)
HEAD_XIAO_5V: J2.1, J2.14, U1.14 (VBUS)
I2C_SCL: J1.5, J12.3, R15.2, U5.22 (SCL)
I2C_SDA: J1.10, J12.2, R14.2, U5.23 (SDA)
I2S_BCLK: J1.3, U8.16 (BCLK)
I2S_DIN: J1.7, U8.1 (DIN)
I2S_LRCLK: J1.12, U8.14 (LRCLK)
LED_L_B: J22.4, R19.2
LED_L_G: J22.3, R18.2
LED_L_R: J22.2, R17.2
LED_R_B: J23.4, R22.2
LED_R_G: J23.3, R21.2
LED_R_R: J23.2, R20.2
MOTOR_STBY: J1.4, U7.19 (STBY)
MOT_A01: J6.1, U7.1 (AO1), U7.2 (AO1)
MOT_A02: J6.2, U7.5 (AO2), U7.6 (AO2)
MOT_B01: J5.1, U7.11 (BO1), U7.12 (BO1)
MOT_B02: J5.2, U7.7 (BO2), U7.8 (BO2)
MUX_RST: J1.11, J12.4, R16.2, U5.3 (~RESET)
PACK_IN: J3.2, Q1.5 (D)
PACK_RP: F1.1, Q1.1 (S), Q1.2 (S), Q1.3 (S)
PFET_GATE: Q1.4 (G), R27.1
PIEZO: J1.8, R1.1
PIEZO_DRV: BZ1.1 (+), R1.2
PWMA: U6.15 (LED8), U7.23 (PWMA)
PWMB: U6.20 (LED13), U7.15 (PWMB)
PWM_LED_L_B: R19.1, U6.8 (LED2)
PWM_LED_L_G: R18.1, U6.7 (LED1)
PWM_LED_L_R: R17.1, U6.6 (LED0)
PWM_LED_R_B: R22.1, U6.11 (LED5)
PWM_LED_R_G: R21.1, U6.10 (LED4)
PWM_LED_R_R: R20.1, U6.9 (LED3)
PWM_SERVO_PAN: R23.1, U6.12 (LED6)
PWM_SERVO_TILT: R24.1, U6.13 (LED7)
SERVO_PAN: J20.1, R23.2
SERVO_TILT: J21.1, R24.2
SPK_VO+: J19.1, U8.9 (OUTP)
SPK_VO-: J19.2, U8.10 (OUTN)
UART0_TX: J1.6, J15.2
VBAT: C9.1, C10.1, C11.1, C19.1, F1.2, J11.4, R25.1, U10.3 (VIN)
XIAO_5V: D1.1 (K), J1.1, J1.14

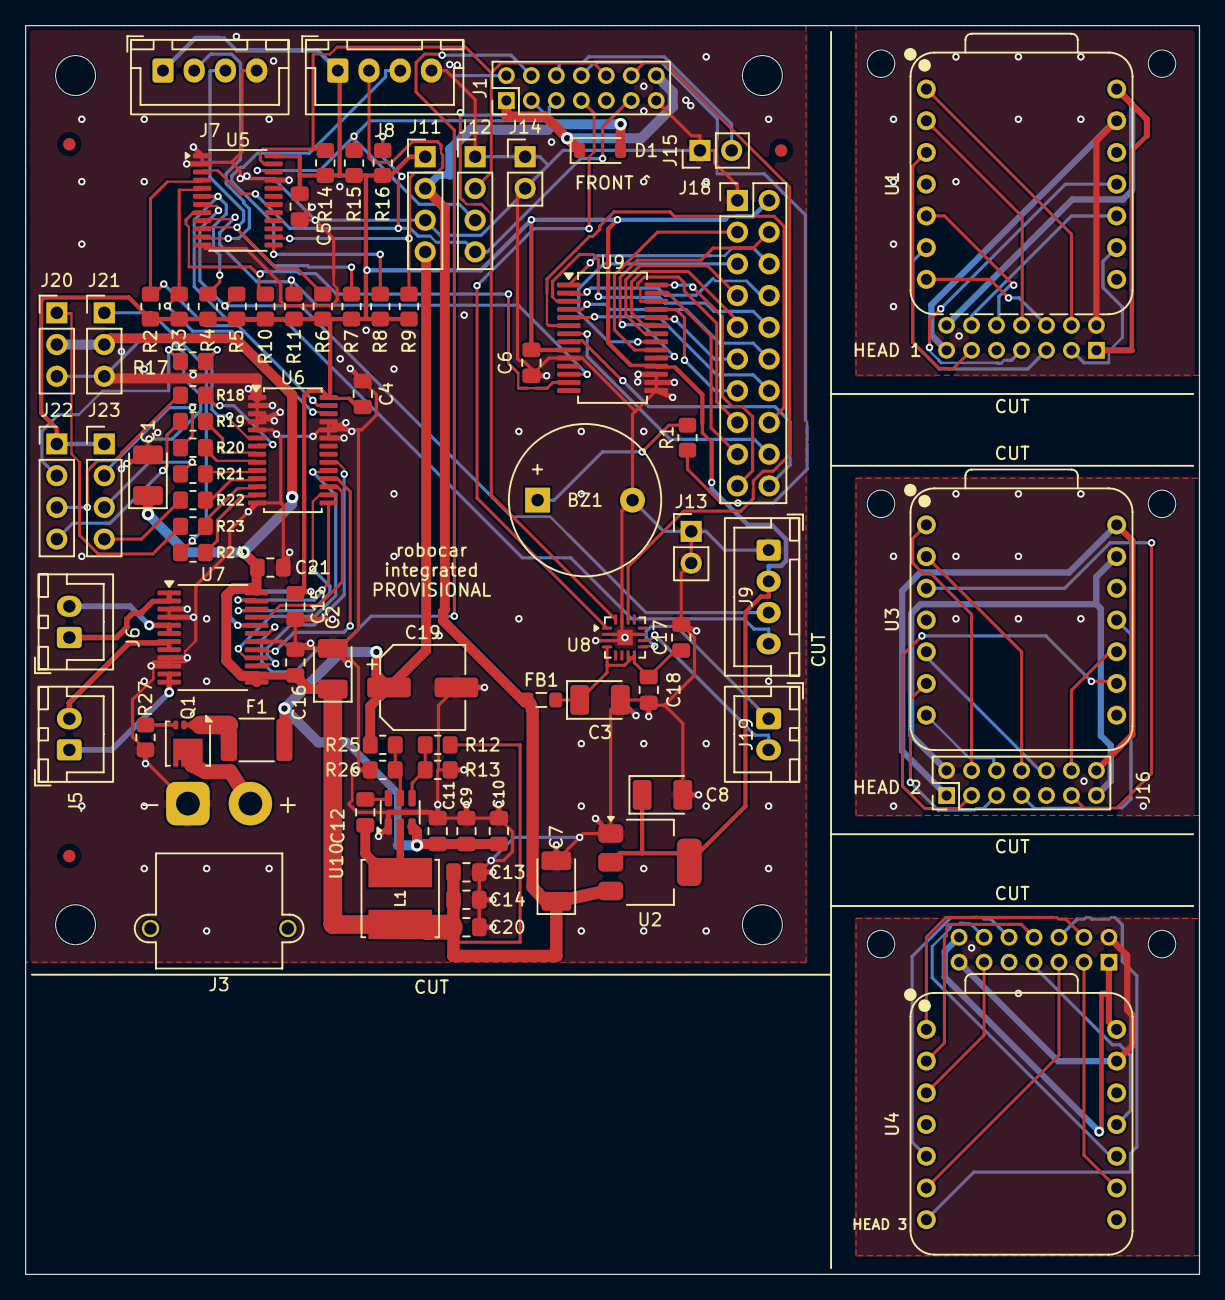
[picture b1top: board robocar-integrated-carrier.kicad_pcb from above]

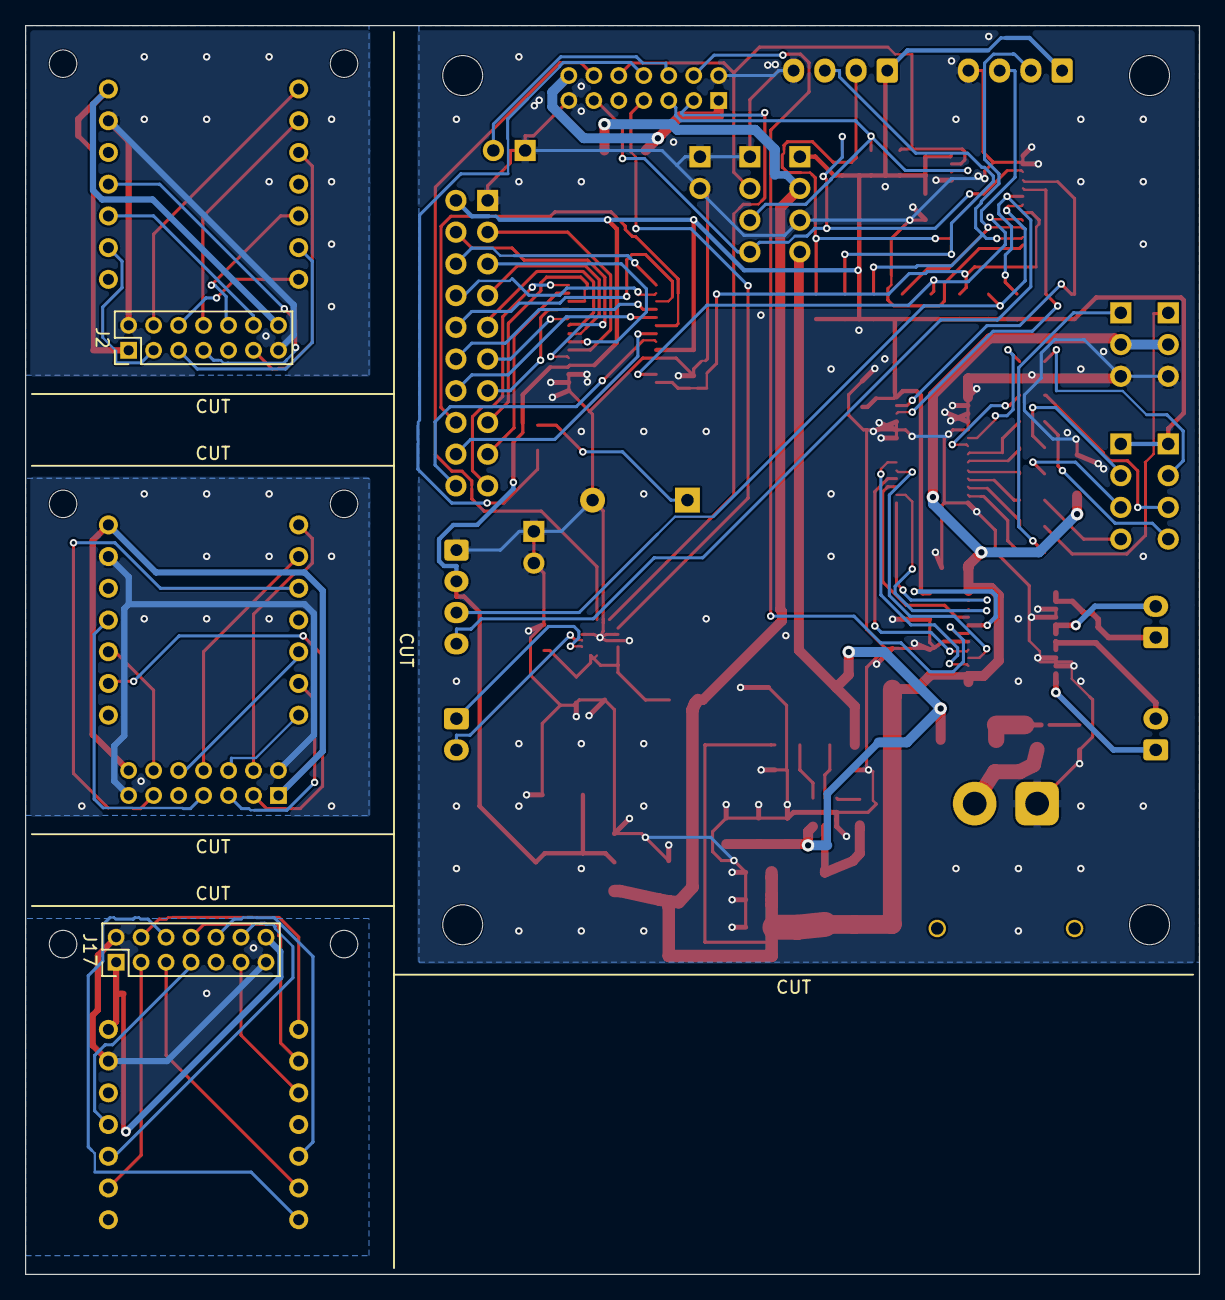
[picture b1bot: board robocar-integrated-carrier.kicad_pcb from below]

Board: 2 copper layers, 94.0 x 100.0 mm, 98 parts (2 on the bottom side), 112 nets.
